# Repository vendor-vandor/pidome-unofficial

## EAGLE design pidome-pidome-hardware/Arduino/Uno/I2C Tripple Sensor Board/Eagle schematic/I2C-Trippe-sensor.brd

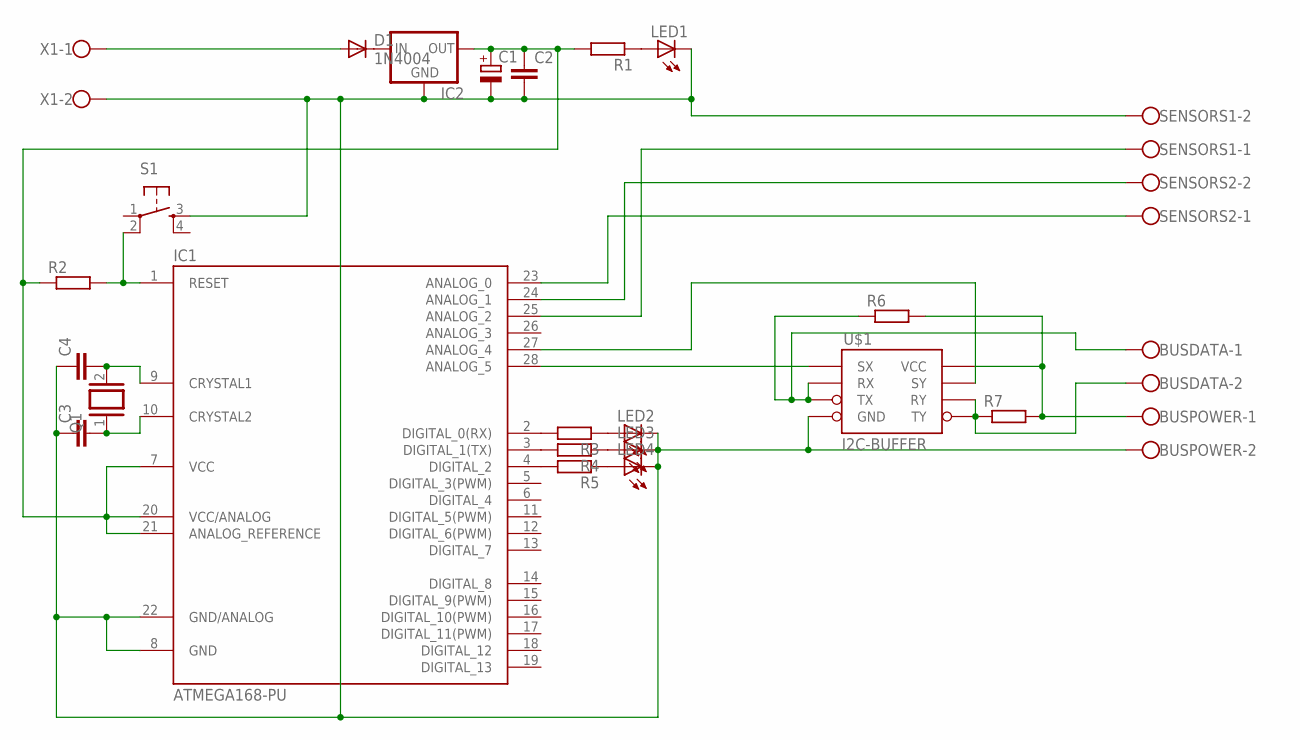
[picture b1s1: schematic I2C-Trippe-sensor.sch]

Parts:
BUSDATA: W237-102
BUSPOWER: W237-102
C1: CPOL-EUE5-10.5; E5-10,5
C2: C-EU050-024X044; C050-024X044
C3, C4: C-EU075-032X103; C075-032X103
D1: 1N4004; DO41-10
IC1: ATMEGA168-PU; DIL28-3
IC2: 78XXL
LED1, LED2, LED3, LED4: LED3MM
Q1: XTAL/S; QS
R1, R2, R3, R4, R5, R6, R7: R-EU_0207/12; 0207/12
S1: TAC_SWITCHPTH; TACTILE-PTH
SENSORS1, SENSORS2: W237-102
U$1: I2C-BUFFER
X1: W237-102

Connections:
unnamed: C4.2, IC1.9 (CRYSTAL1), Q1.2
unnamed: C3.2, IC1.10 (CRYSTAL2), Q1.1
unnamed: LED1.A, R1.1
unnamed: D1.C, IC2.IN
unnamed: IC1.3 (DIGITAL_1(TX)), R4.2
unnamed: IC1.2 (DIGITAL_0(RX)), R3.2
unnamed: BUSPOWER.1, R6.2, R7.2, U$1.8 (VCC)
unnamed: BUSDATA.2, R7.1, U$1.5 (TY), U$1.6 (RY)
unnamed: BUSDATA.1, R6.1, U$1.2 (RX), U$1.3 (TX)
unnamed: LED2.A, R3.1
unnamed: LED3.A, R4.1
unnamed: IC1.25 (ANALOG_2), SENSORS1.1
unnamed: C1.+, C2.1, IC1.7 (VCC), IC1.20 (VCC/ANALOG), IC1.21 (ANALOG_REFERENCE), IC2.OUT, R1.2, R2.1
unnamed: D1.A, X1.1
unnamed: IC1.23 (ANALOG_0), SENSORS2.1
unnamed: LED4.A, R5.1
unnamed: IC1.1 (RESET), R2.2, S1.2
unnamed: IC1.4 (DIGITAL_2), R5.2
unnamed: BUSPOWER.2, C1.-, C2.2, C3.1, C4.1, IC1.8 (GND), IC1.22 (GND/ANALOG), IC2.GND, LED1.K (C), LED2.K (C), LED3.K (C), LED4.K (C), S1.3, SENSORS1.2, U$1.4 (GND), X1.2
unnamed: IC1.24 (ANALOG_1), SENSORS2.2
unnamed: IC1.28 (ANALOG_5), U$1.1 (SX)
unnamed: IC1.27 (ANALOG_4), U$1.7 (SY)

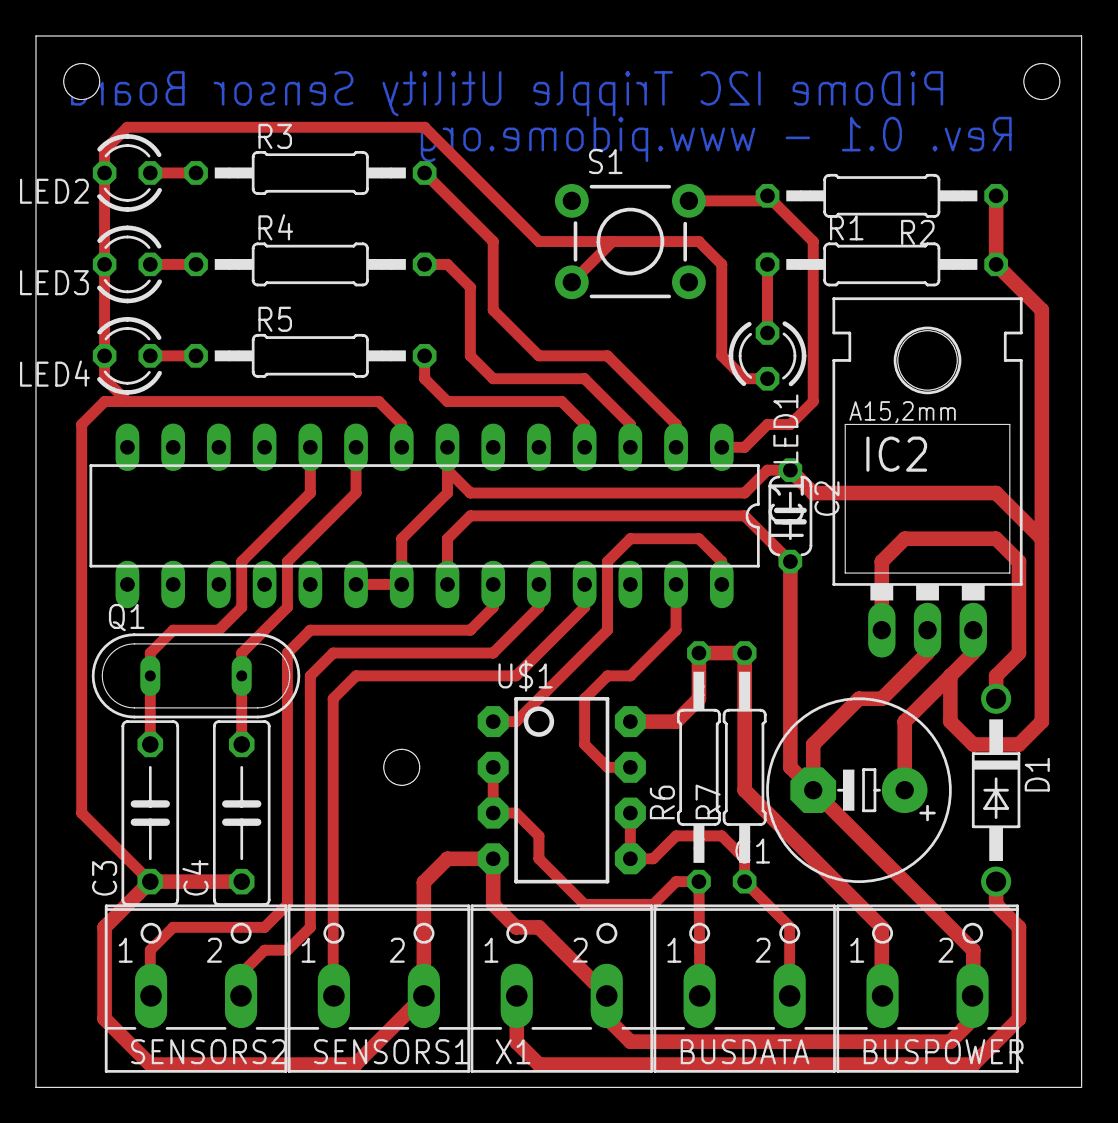
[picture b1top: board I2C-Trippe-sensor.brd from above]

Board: 2 copper layers, 58.1 x 58.4 mm, 26 parts (0 on the bottom side), 22 nets.

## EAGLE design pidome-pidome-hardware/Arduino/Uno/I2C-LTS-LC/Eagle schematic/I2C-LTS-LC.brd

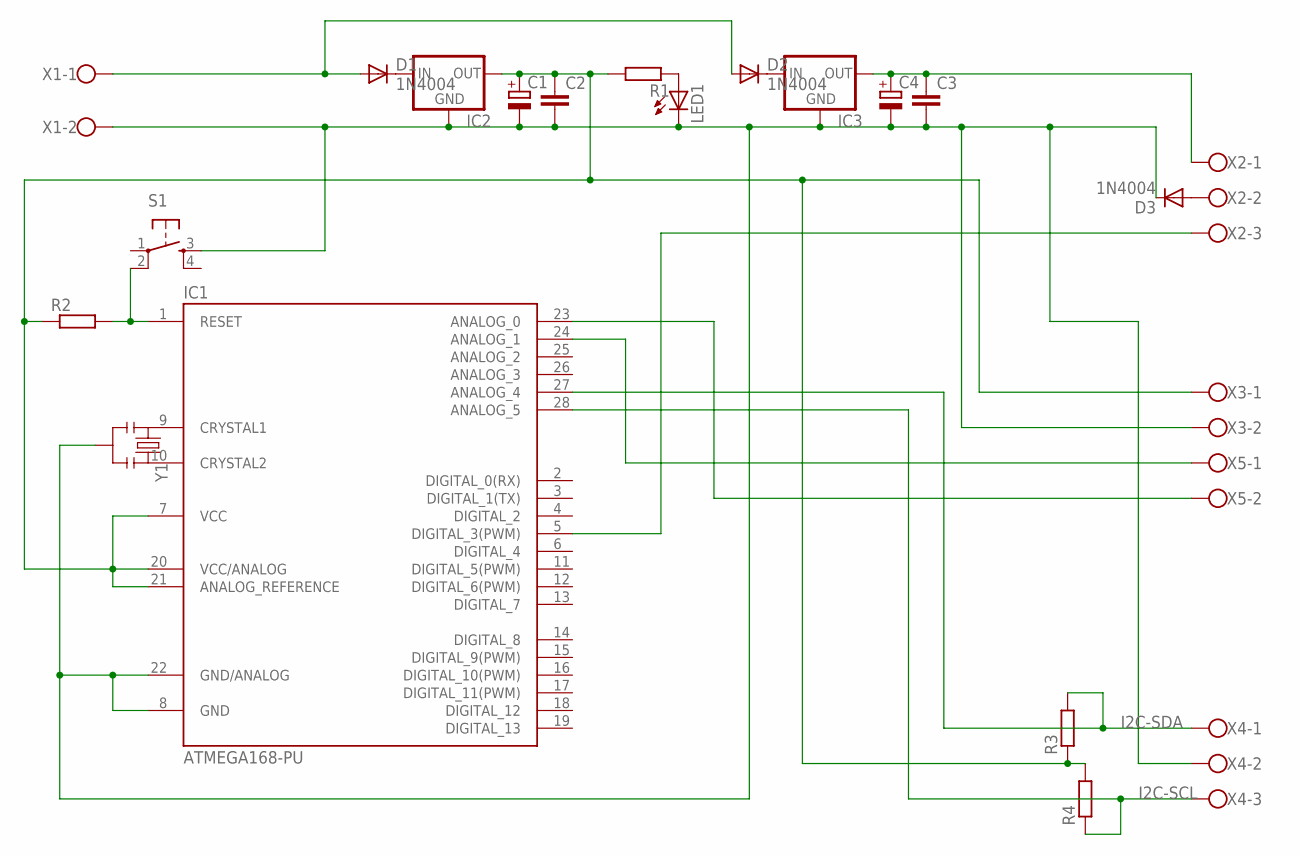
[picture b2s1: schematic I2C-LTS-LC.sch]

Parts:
C1, C4: CPOL-EUE5-10.5; E5-10,5
C2, C3: C-EU050-024X044; C050-024X044
D1, D2, D3: 1N4004; DO41-10
IC1: ATMEGA168-PU; DIL28-3
IC2, IC3: 78XXL
LED1: LED3MM
R1, R2, R3, R4: R-EU_0207/12; 0207/12
S1: TAC_SWITCHPTH; TACTILE-PTH
X1, X3, X5: W237-102
X2, X4: W237-103
Y1: RESONATORPTH; RESONATOR-PTH

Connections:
I2C-SCL: IC1.28 (ANALOG_5), R4.1, X4.3
I2C-SDA: IC1.27 (ANALOG_4), R3.2, X4.1
unnamed: IC1.10 (CRYSTAL2), Y1.3
unnamed: IC1.9 (CRYSTAL1), Y1.1
unnamed: LED1.A, R1.1
unnamed: D1.C, IC2.IN
unnamed: D2.C, IC3.IN
unnamed: D3.A, X2.2
unnamed: IC1.5 (DIGITAL_3(PWM)), X2.3
unnamed: C1.-, C2.2, C3.2, C4.-, D3.C, IC1.8 (GND), IC1.22 (GND/ANALOG), IC2.GND, IC3.GND, LED1.K (C), S1.3, X1.2, X3.2, X4.2, Y1.2
unnamed: IC1.23 (ANALOG_0), X5.2
unnamed: IC1.24 (ANALOG_1), X5.1
unnamed: C3.1, C4.+, IC3.OUT, X2.1
unnamed: C1.+, C2.1, IC1.7 (VCC), IC1.20 (VCC/ANALOG), IC1.21 (ANALOG_REFERENCE), IC2.OUT, R1.2, R2.1, R3.1, R4.2, X3.1
unnamed: D1.A, D2.A, X1.1
unnamed: IC1.1 (RESET), R2.2, S1.2

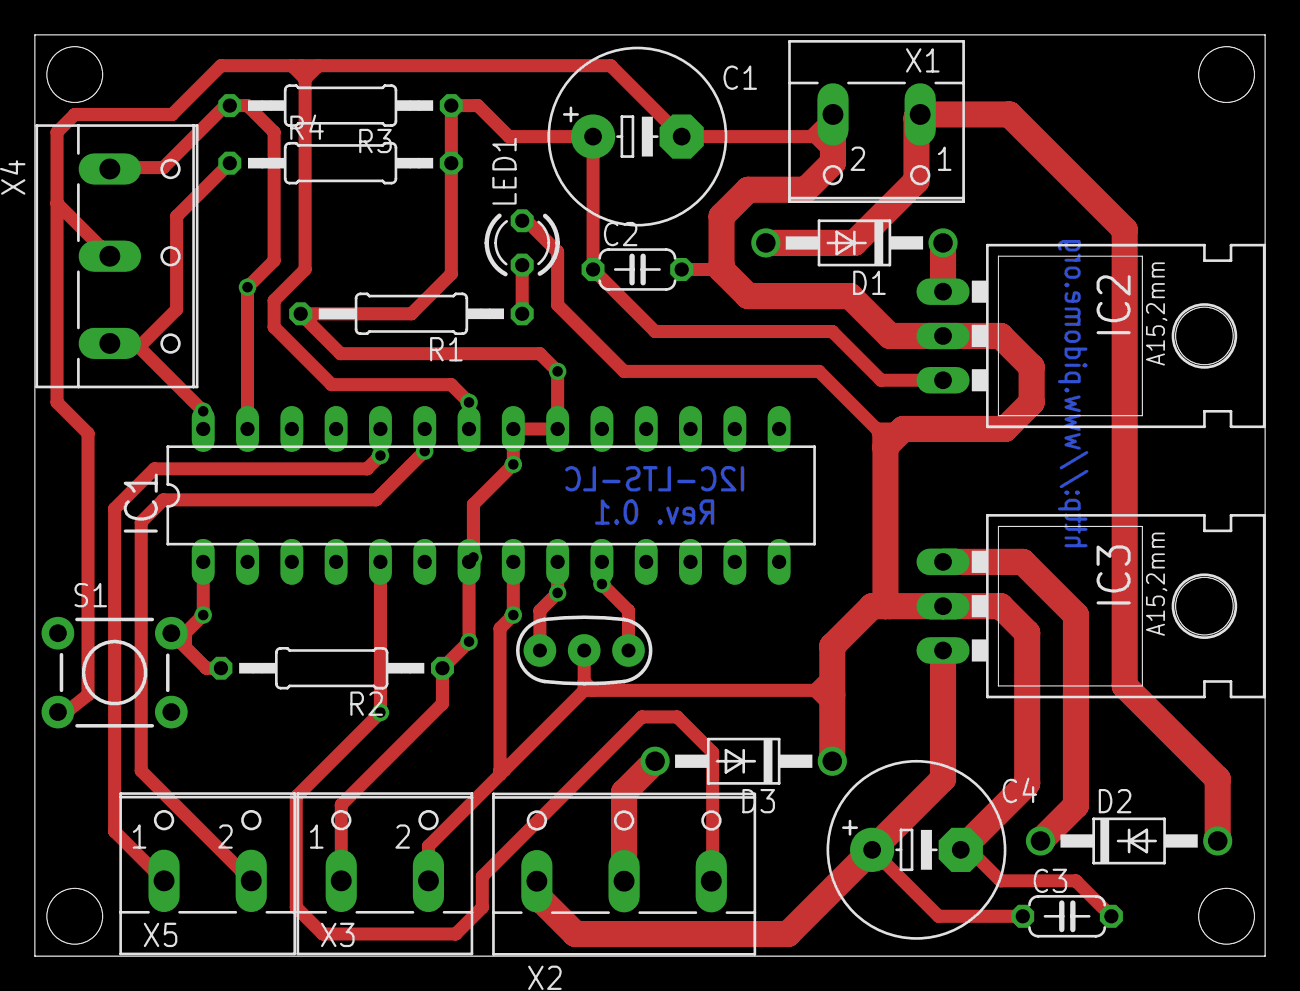
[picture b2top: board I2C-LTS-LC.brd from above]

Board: 2 copper layers, 70.5 x 52.8 mm, 22 parts (0 on the bottom side), 16 nets.

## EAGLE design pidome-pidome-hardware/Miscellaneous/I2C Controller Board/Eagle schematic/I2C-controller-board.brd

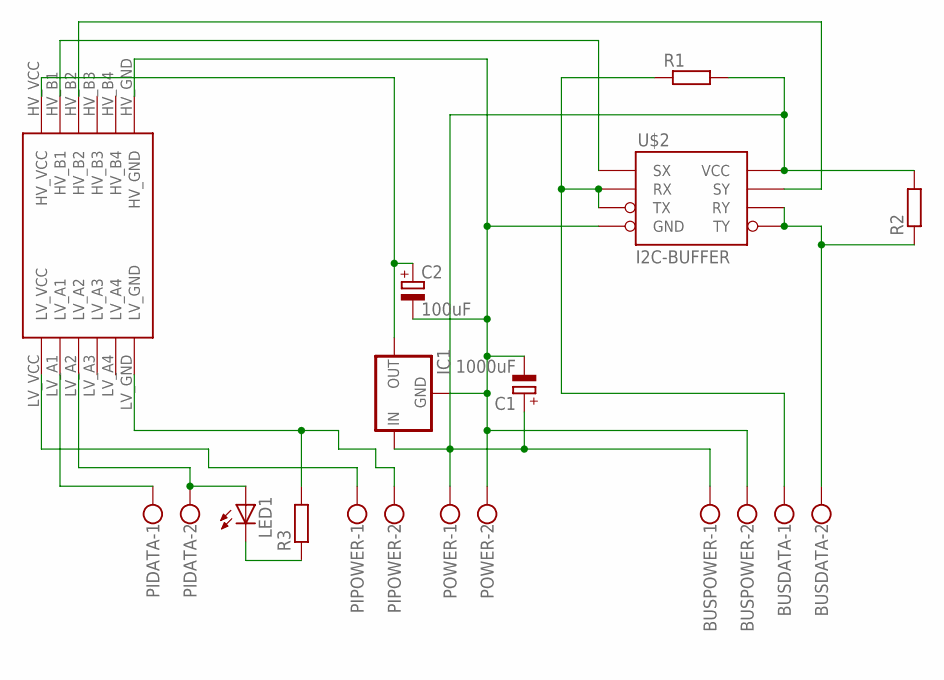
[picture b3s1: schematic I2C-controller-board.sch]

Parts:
BUSDATA: W237-102
BUSPOWER: W237-102
C1: 1000uF; E5-10,5
C2: 100uF; E2,5-6
IC1: 78XXL
LED1: LED5MM
PIDATA: W237-102
PIPOWER: W237-102
POWER: W237-102
R1, R2, R3: R-EU_0204/7; 0204/7
U$2: I2C-BUFFER
U$3: SPARKFUN_LEVEL_SHIFTER

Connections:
unnamed: PIDATA.1, U$3.LV_A1
unnamed: U$2.1 (SX), U$3.HV_B1
unnamed: PIPOWER.1, U$3.LV_VCC
unnamed: U$2.7 (SY), U$3.HV_B2
unnamed: LED1.K (C), R3.1
unnamed: BUSPOWER.1, C1.+, IC1.IN, POWER.1, R1.2, R2.2, U$2.8 (VCC)
unnamed: BUSPOWER.2, C1.-, C2.-, IC1.GND, POWER.2, U$2.4 (GND), U$3.HV_GND
unnamed: C2.+, IC1.OUT, U$3.HV_VCC
unnamed: LED1.A, PIDATA.2, U$3.LV_A2
unnamed: PIPOWER.2, R3.2, U$3.LV_GND
unnamed: BUSDATA.2, R2.1, U$2.5 (TY), U$2.6 (RY)
unnamed: BUSDATA.1, R1.1, U$2.2 (RX), U$2.3 (TX)

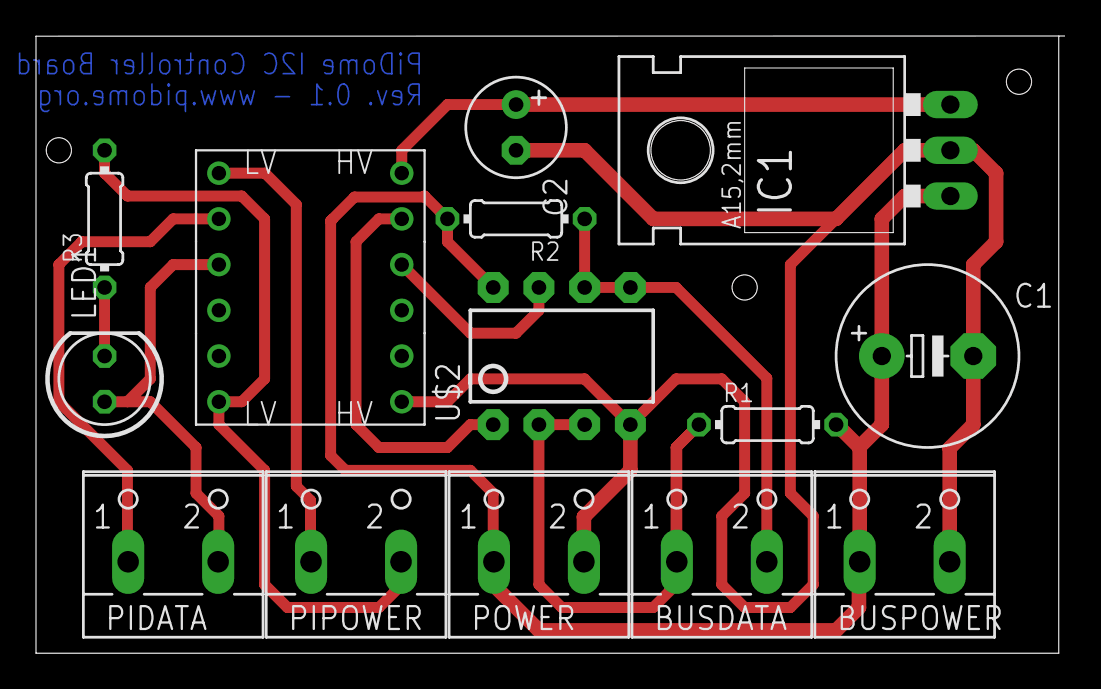
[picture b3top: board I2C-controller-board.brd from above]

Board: 2 copper layers, 57.1 x 34.3 mm, 14 parts (0 on the bottom side), 12 nets.

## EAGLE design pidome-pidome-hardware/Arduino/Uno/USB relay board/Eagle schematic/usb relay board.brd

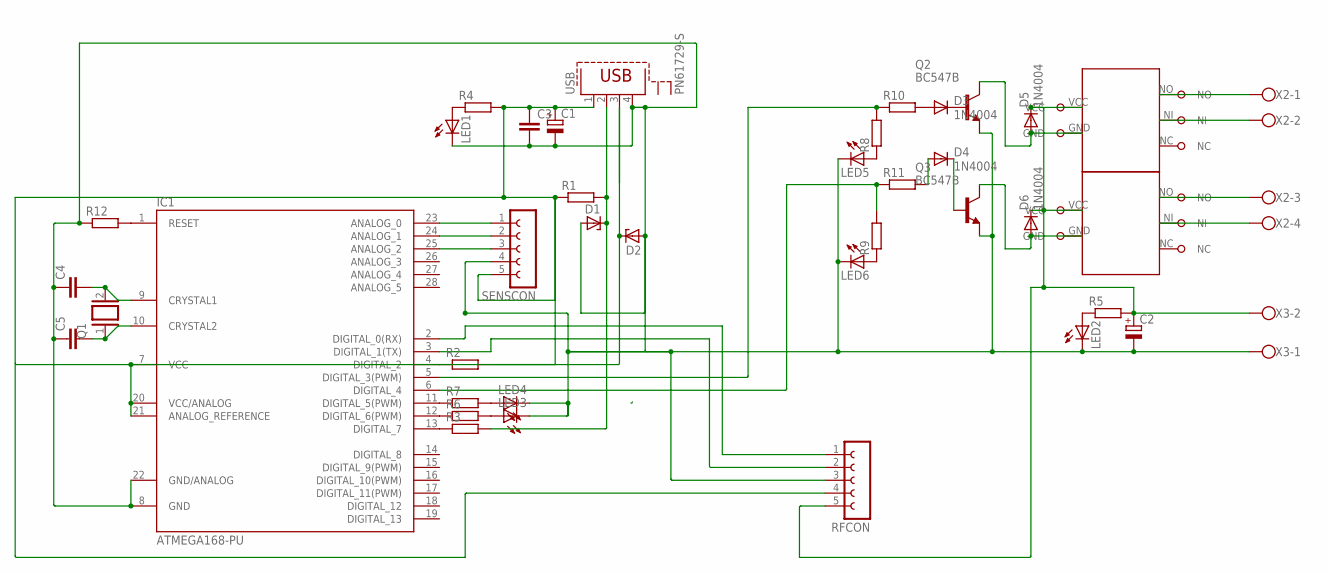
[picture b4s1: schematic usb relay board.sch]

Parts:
C1: CPOL-EUE2.5-7; E2,5-7
C2: CPOL-EUE5-10.5; E5-10,5
C3, C4, C5: C-EU075-032X103; C075-032X103
D1, D2: ZENER-DIODEDO34-7; DO34Z7
D3, D4, D5, D6: 1N4004; DO41-10
IC1: ATMEGA168-PU; DIL28-3
LED1, LED2, LED3, LED4, LED5, LED6: LED3MM
Q1: XTAL/S; QS
Q2, Q3: BC547B; TO92
R1, R2, R3, R4, R5, R6, R7, R8, R9, R10, R11, R12: R-EU_0204/7; 0204/7
RFCON: FE05-1
SENSCON: FE05-1
U$1, U$2: RELAY
USB: PN61729-S
X2: W237-4
X3: W237-102

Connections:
unnamed: U$2.NO, X2.3
unnamed: D6.A, Q3.3 (C), U$2.GND
unnamed: D5.A, Q2.3 (C), U$1.GND
unnamed: U$2.NI, X2.4
unnamed: C4.2, IC1.9 (CRYSTAL1), Q1.2
unnamed: C5.2, IC1.10 (CRYSTAL2), Q1.1
unnamed: C1.-, C2.-, C3.2, C4.1, C5.1, D1.A, D2.A, IC1.8 (GND), IC1.22 (GND/ANALOG), LED1.K (C), LED2.K (C), LED3.K (C), LED4.K (C), LED5.K (C), LED6.K (C), Q2.1 (E), Q3.1 (E), R12.1, RFCON.3, SENSCON.4, USB.4, X3.1
unnamed: IC1.1 (RESET), R12.2
unnamed: IC1.12 (DIGITAL_6(PWM)), R6.1
unnamed: IC1.11 (DIGITAL_5(PWM)), R7.1
unnamed: LED3.A, R6.2
unnamed: LED4.A, R7.2
unnamed: IC1.13 (DIGITAL_7), R3.1
unnamed: IC1.4 (DIGITAL_2), R2.1
unnamed: LED1.A, R4.1
unnamed: D1.C, R1.2, R3.2, USB.2
unnamed: D2.C, R2.2, USB.3
unnamed: IC1.6 (DIGITAL_4), R9.2, R11.1
unnamed: C1.+, C3.1, IC1.7 (VCC), IC1.20 (VCC/ANALOG), IC1.21 (ANALOG_REFERENCE), R1.1, R4.2, SENSCON.5, USB.1
unnamed: LED2.A, R5.1
unnamed: D3.C, Q2.2 (B)
unnamed: D4.C, Q3.2 (B)
unnamed: D3.A, R10.2
unnamed: D4.A, R11.2
unnamed: U$1.NI, X2.2
unnamed: IC1.5 (DIGITAL_3(PWM)), R8.2, R10.1
unnamed: LED5.A, R8.1
unnamed: LED6.A, R9.1
unnamed: U$1.NO, X2.1
unnamed: IC1.23 (ANALOG_0), SENSCON.1
unnamed: C2.+, D5.C, D6.C, R5.2, RFCON.5, U$1.VCC, U$2.VCC, X3.2
unnamed: IC1.24 (ANALOG_1), SENSCON.2
unnamed: IC1.25 (ANALOG_2), SENSCON.3
unnamed: IC1.2 (DIGITAL_0(RX)), RFCON.1
unnamed: IC1.3 (DIGITAL_1(TX)), RFCON.2

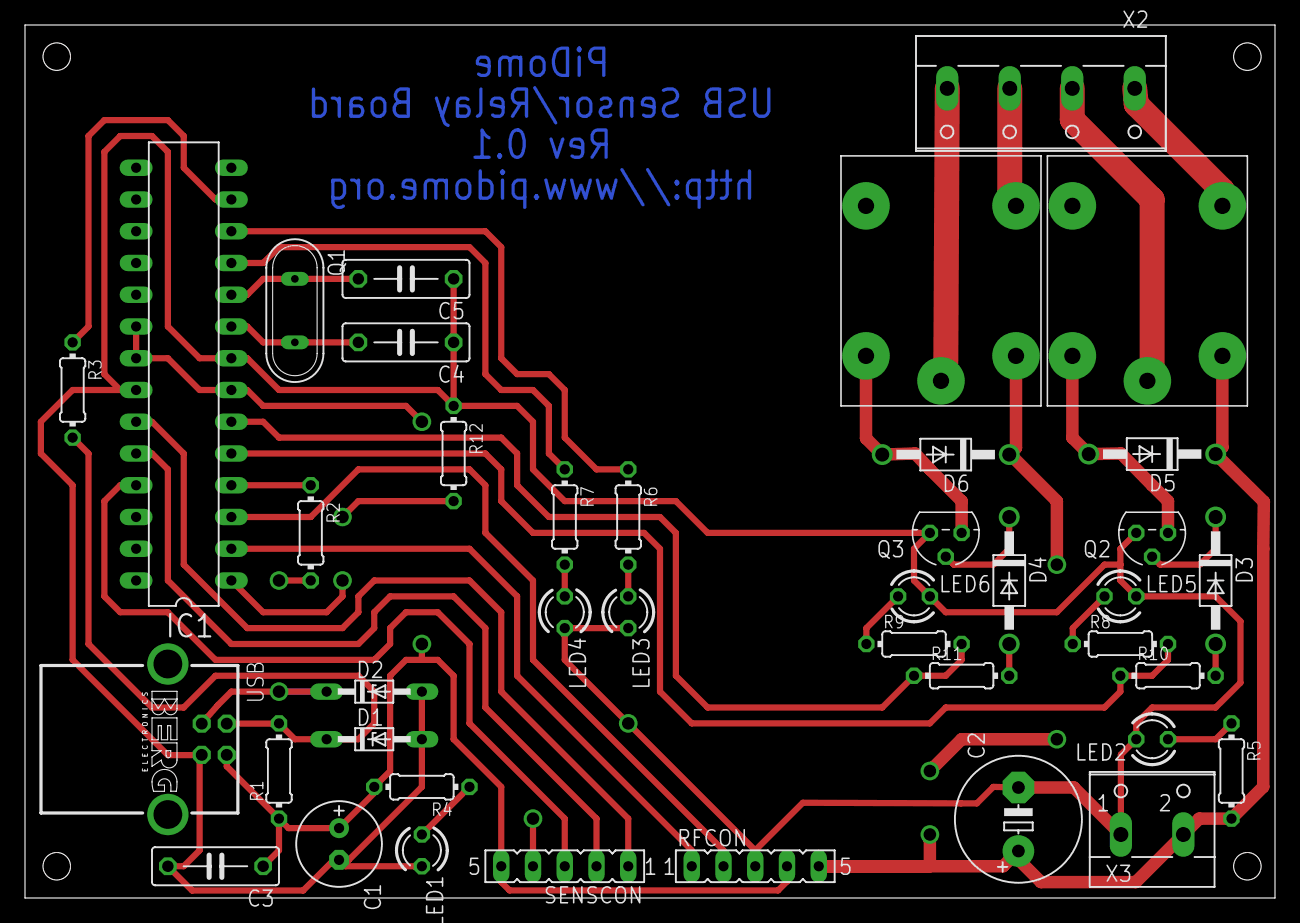
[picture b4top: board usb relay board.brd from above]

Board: 2 copper layers, 100.0 x 69.8 mm, 40 parts (0 on the bottom side), 35 nets.

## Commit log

2016-03-04 clone from bitbucket

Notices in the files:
parts and their libraries:
SparkFun-Electromechanical: Licensing: CC v3.0 Share-Alike You are welcome to use this library for commercial purposes.
